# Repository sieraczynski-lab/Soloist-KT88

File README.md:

# Soloist 88 — stereofoniczny wzmacniacz lampowy na KT88

Projekt DIY wzmacniacza lampowego w stereo, opartego na układzie **Mullard 5-20** w wersji TubeMack „Soloist” przerobionej na **KT88**:

**EF86 → E88CC (odwracacz z długim ogonem, źródło prądowe DN2540) → 2× KT88 w układzie ultraliniowym, bias stały ≈ −80 V**

Do tego sterowanie na **ESP32-S3**: sekwencja włączania, pomiar prądu każdej KT88, automatyczna korekta biasu, przełącznik UL/trioda, przełącznik kolumn Marantz / Lampa i wejście trigger 12 V z amplitunera. Na wejściu **selektor 4 wejść z przekaźnikową drabinką głośności** 0–63 dB.

> ⚠️ **Wysokie napięcie.** W tym urządzeniu jest do ok. 560 V DC i 230 V AC. Kondensatory trzymają ładunek po wyłączeniu. Budujesz i uruchamiasz na własną odpowiedzialność, a pierwsze włączenia rób przez żarówkę szeregową, zgodnie z [procedurą uruchomienia](docs/06-uruchomienie.md).

## Najważniejsze parametry (z obliczeń, jeszcze nie z pomiarów)

| | |
|---|---|
| Moc | ok. 45 W na kanał na 4 Ω (zasilacz liczony na tę moc ciągłą) |
| Czułość | ok. 160 mV na pełną moc (dobierana R104) |
| Sprzężenie zwrotne | 14–16 dB |
| B+ | ok. 465 V, KT88 ok. 55 mA, ok. 25 W strat na lampę |
| Transformatory wyjściowe | Toroidy.pl TTG-KT88PP, 4 kΩ, UL |
| Transformator sieciowy | toroid 400 VA, jeden na oba kanały |

## Zawartość repozytorium

| Katalog | Co tam jest |
|---|---|
| [`docs/`](docs/) | dokumentacja: układ, zasilanie, sterowanie, płytki, obudowa, uruchomienie, zakupy, decyzje |
| [`hardware/pcb/`](hardware/pcb/) | gotowe pliki płytek: import do EasyEDA Pro, projekty KiCad, PDF-y rozmieszczenia, BOM do JLCPCB i LCSC, [`CZYTAJ_MNIE.txt`](hardware/pcb/CZYTAJ_MNIE.txt) |
| [`hardware/selektor/`](hardware/selektor/) | selektor wejść z drabinką głośności: projekt KiCad 8, eksport do EasyEDA Pro, BOM do JLCPCB i LCSC |
| [`hardware/case/`](hardware/case/) | obudowa: STEP (do Fusion 360), DXF do cięcia laserem, lista części, widoki |
| [`site/index.html`](site/index.html) | strona projektu: schematy, punkty pracy, sekwencja, zabezpieczenia, lista elementów |
| [`src/`](src/) | skrypty w Pythonie, które generują wszystko powyżej ([jak uruchomić](src/README.md)) |

## Płytki

| Płytka | Rozmiar | Ilość | Opis |
|---|---|---|---|
| `kanal` | 100 × 100 mm | 2 | EF86, E88CC, źródło prądowe, sieć biasu i sprzężenia zwrotnego |
| `zasilacz_siec` | 100 × 100 mm | 1 | miękki start K1/K2, bezpieczniki F2/F3, prostownik biasu, żarzenie |
| `zasilacz_hv` | 100 × 100 mm | 1 | K3/K4, mostek UF5408, kondensatory C1/C2, dzielnik pomiaru B+, LED HV |
| `sterowanie` | 100 × 100 mm | 1 | ESP32-S3, 2× ADS1115, MCP4728 + LM324, ULN2803, IRM-15-12; elementy SMD montuje JLCPCB |
| `ul` | 74 × 48 mm | 2 | przekaźniki UL/trioda (G2RL-2), jeden na KT88 |
| `glosniki` | 100 × 42 mm | 1 | przełącznik kolumn Marantz / Lampa (2× G2RL-2) |
| [`selektor`](hardware/selektor/) | 96 × 74 mm | 1 | 4 wejścia, drabinka 0–63 dB co 1 dB, mute fail-safe; 11× G6K-2F-Y, MCP23017 (I²C 0x20), 2× ULN2803; tylko 12 V |

## Dokumentacja

1. [Układ i punkty pracy](docs/01-uklad.md)
2. [Zasilanie i transformatory](docs/02-zasilanie.md)
3. [Sterowanie ESP32: korekta biasu, UL/trioda, kolumny, trigger](docs/03-sterowanie.md)
4. [Płytki PCB: EasyEDA, klasy sieci, JLCPCB](docs/04-plytki-pcb.md)
5. [Obudowa](docs/05-obudowa.md)
6. [Uruchomienie krok po kroku](docs/06-uruchomienie.md)
7. [Źródła sygnału i poziomy (WiiM, Marantz, selektor)](docs/07-zrodla-i-poziomy.md)
8. [Części i zakupy: lampy, przewody, przekaźniki, BOM](docs/08-czesci-i-zakupy.md)
9. [Historia decyzji i poprawek](docs/09-historia-decyzji.md)
10. [Do zrobienia / do sprawdzenia](docs/10-do-zrobienia.md)
11. [Selektor wejść i drabinka głośności](docs/11-selektor.md)
12. [Warianty lamp (opcjonalne)](docs/12-warianty-lamp.md)

## Stan

- Płytki: wersja **0.23**. Kanał po routingu w EasyEDA (wersja 0.21, od tamtej pory bez zmian). Pozostałe płytki do routingu.
- Selektor: wersja **0.5**, schemat gotowy, elementy rozmieszczone, do routingu ([szczegóły](docs/11-selektor.md)).
- Obudowa: wersja **0.4**.
- Strona projektu: wersja **0.12**.
- Program ESP32: opisany (sekwencje, algorytmy, progi), jeszcze nienapisany.
- Przed zamówieniem płytek: [lista rzeczy do sprawdzenia](docs/10-do-zrobienia.md#przed-zamówieniem-płytek).

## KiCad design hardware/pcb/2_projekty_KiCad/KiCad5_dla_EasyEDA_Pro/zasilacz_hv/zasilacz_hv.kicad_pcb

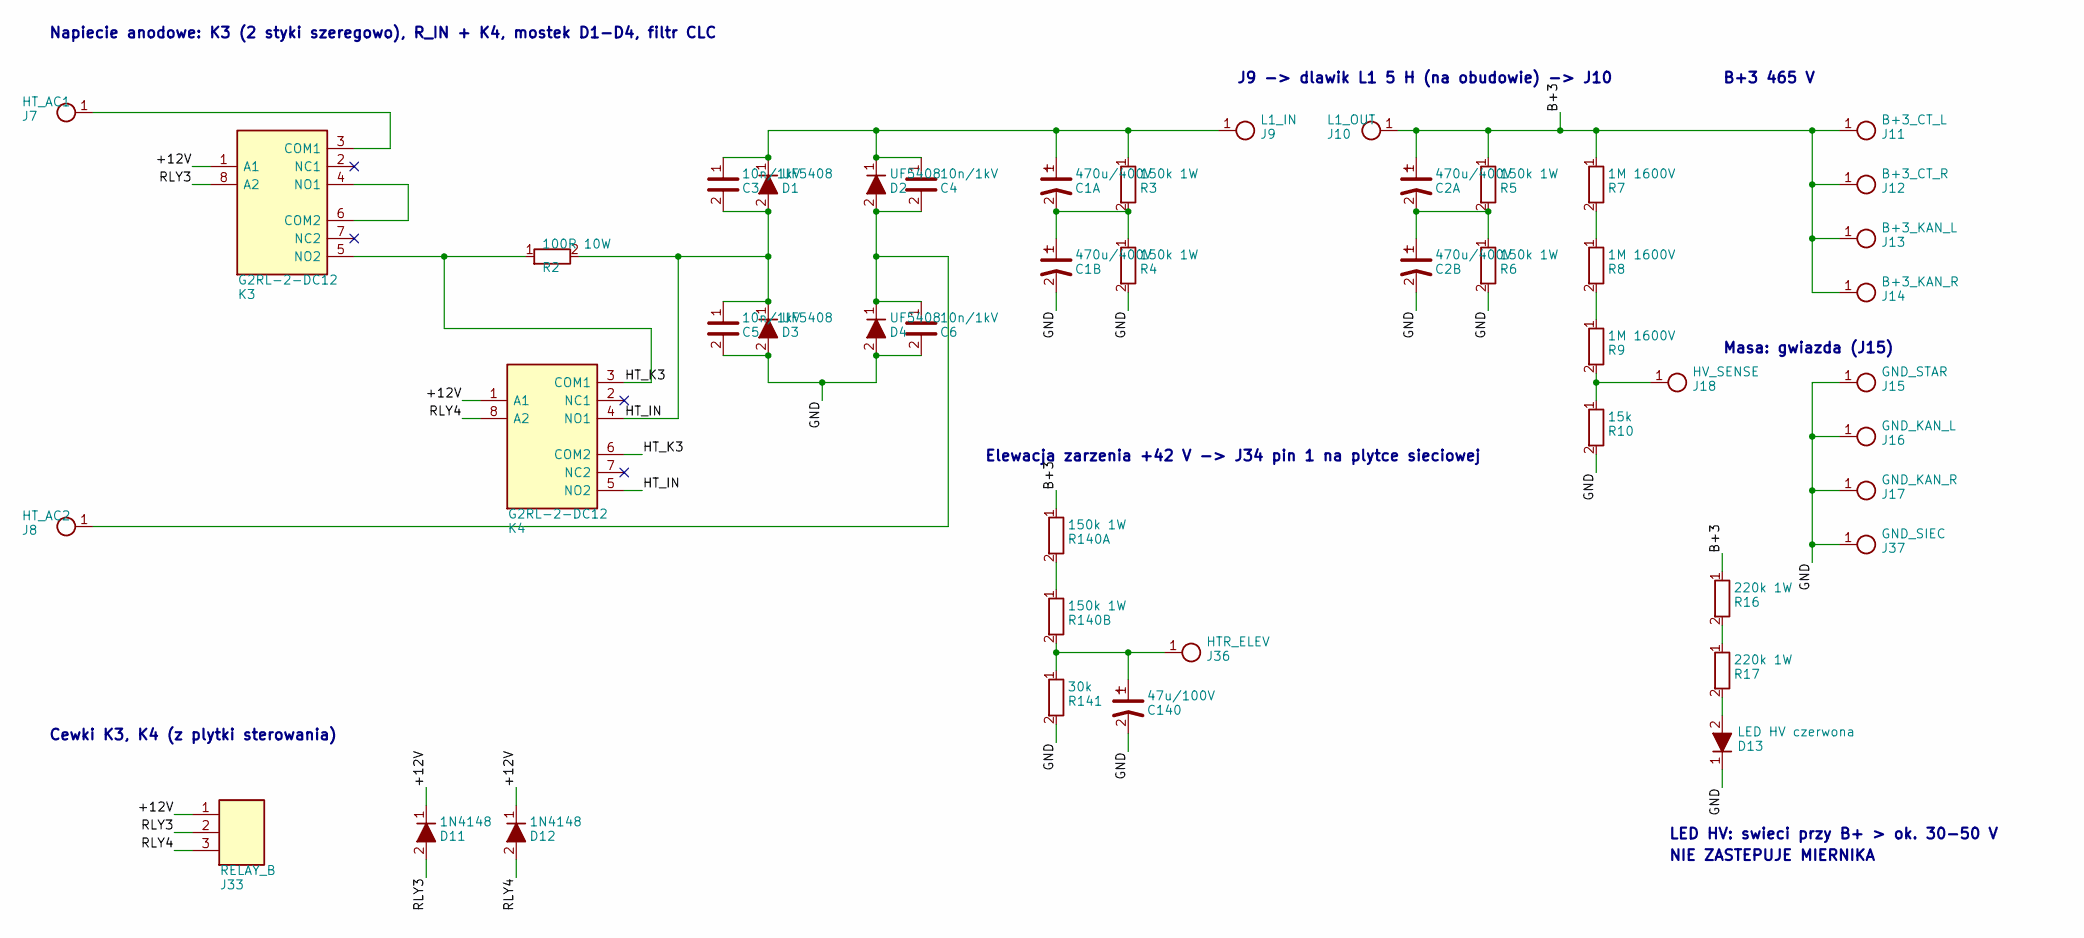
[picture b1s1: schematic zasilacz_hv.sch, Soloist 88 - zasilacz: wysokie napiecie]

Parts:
C1A, C1B, C2A, C2B: 470u/400V; CP_SnapIn_D30_P10
C3, C4, C5, C6: 10n/1kV; C_Disc_1kV_P10_V
C140: 47u/100V; CP_Radial_D10_P5
D1, D2, D3, D4: UF5408; D_DO-201_P15.24_V
D11: 1N4148; D_DO-35_P7.62
D12: 1N4148; D_DO-35_P7.62_V
D13: LED HV czerwona; LED_D3.0_P2.54
J7: HT_AC1; WirePad_4.5
J8: HT_AC2; WirePad_4.5
J9: L1_IN; WirePad_4.5
J10: L1_OUT; WirePad_4.5
J11: B+3_CT_L; WirePad_4.5
J12: B+3_CT_R; WirePad_4.5
J13: B+3_KAN_L; WirePad_4.5
J14: B+3_KAN_R; WirePad_4.5
J15: GND_STAR; WirePad_4.5
J16: GND_KAN_L; WirePad_4.5
J17: GND_KAN_R; WirePad_4.5
J18: HV_SENSE; WirePad_3.5
J33: RELAY_B; PinHeader_1x03_P2.54_H
J36: HTR_ELEV; WirePad_3.5
J37: GND_SIEC; WirePad_4.5
K3, K4: G2RL-2-DC12; Relay_DPDT_Omron_G2RL
R2: 100R 10W; R_Cement_10W_P55.88
R3, R4, R140A: 150k 1W; R_Axial_1W_P15.24_V
R5, R6, R140B: 150k 1W; R_Axial_1W_P15.24
R7, R8, R9: 1M 1600V; R_Axial_1W_P15.24_V
R10: 15k; R_Axial_0.5W_P12.7_V
R16, R17: 220k 1W; R_Axial_1W_P15.24
R141: 30k; R_Axial_0.5W_P12.7

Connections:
+12V: D11.1 (K), D12.1 (K), J33.1, K3.1 (A1), K4.1 (A1)
B+3: C2A.1, J10.1, J11.1, J12.1, J13.1, J14.1, R5.1, R7.1, R16.1, R140A.1
C1_MID: C1A.2, C1B.1, R3.2, R4.1
C2_MID: C2A.2, C2B.1, R5.2, R6.1
ELEV_MID: R140A.2, R140B.1
GND: C1B.2, C2B.2, C5.2, C6.2, C140.2, D3.2 (A), D4.2 (A), D13.1 (K), J15.1, J16.1, J17.1, J37.1, R4.2, R6.2, R10.2, R141.2
HTR_ELEV: C140.1, J36.1, R140B.2, R141.1
HT_AC1: J7.1, K3.3 (COM1)
HT_AC2: C4.2, C6.1, D2.2 (A), D4.1 (K), J8.1
HT_IN: C3.2, C5.1, D1.2 (A), D3.1 (K), K4.4 (NO1), K4.5 (NO2), R2.2
HT_K3: K3.5 (NO2), K4.3 (COM1), K4.6 (COM2), R2.1
HVS1: R7.2, R8.1
HVS2: R8.2, R9.1
HV_RAW: C1A.1, C3.1, C4.1, D1.1 (K), D2.1 (K), J9.1, R3.1
HV_SENSE: J18.1, R9.2, R10.1
K3_MID: K3.4 (NO1), K3.6 (COM2)
LED_A: D13.2 (A), R17.2
LED_M: R16.2, R17.1
RLY3: D11.2 (A), J33.2, K3.8 (A2)
RLY4: D12.2 (A), J33.3, K4.8 (A2)

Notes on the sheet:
Napiecie anodowe: K3 (2 styki szeregowo), R_IN + K4, mostek D1-D4, filtr CLC
J9 -> dlawik L1 5 H (na obudowie) -> J10
B+3 465 V
Elewacja zarzenia +42 V -> J34 pin 1 na plytce sieciowej
Cewki K3, K4 (z plytki sterowania)
LED HV: swieci przy B+ > ok. 30-50 V
NIE ZASTEPUJE MIERNIKA
Masa: gwiazda (J15)

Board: 2 copper layers, 51 parts (2 on the bottom side), 20 nets, no tracks yet.

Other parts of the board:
MH1, MH2, MH3, MH4: M3; MountingHole_M3

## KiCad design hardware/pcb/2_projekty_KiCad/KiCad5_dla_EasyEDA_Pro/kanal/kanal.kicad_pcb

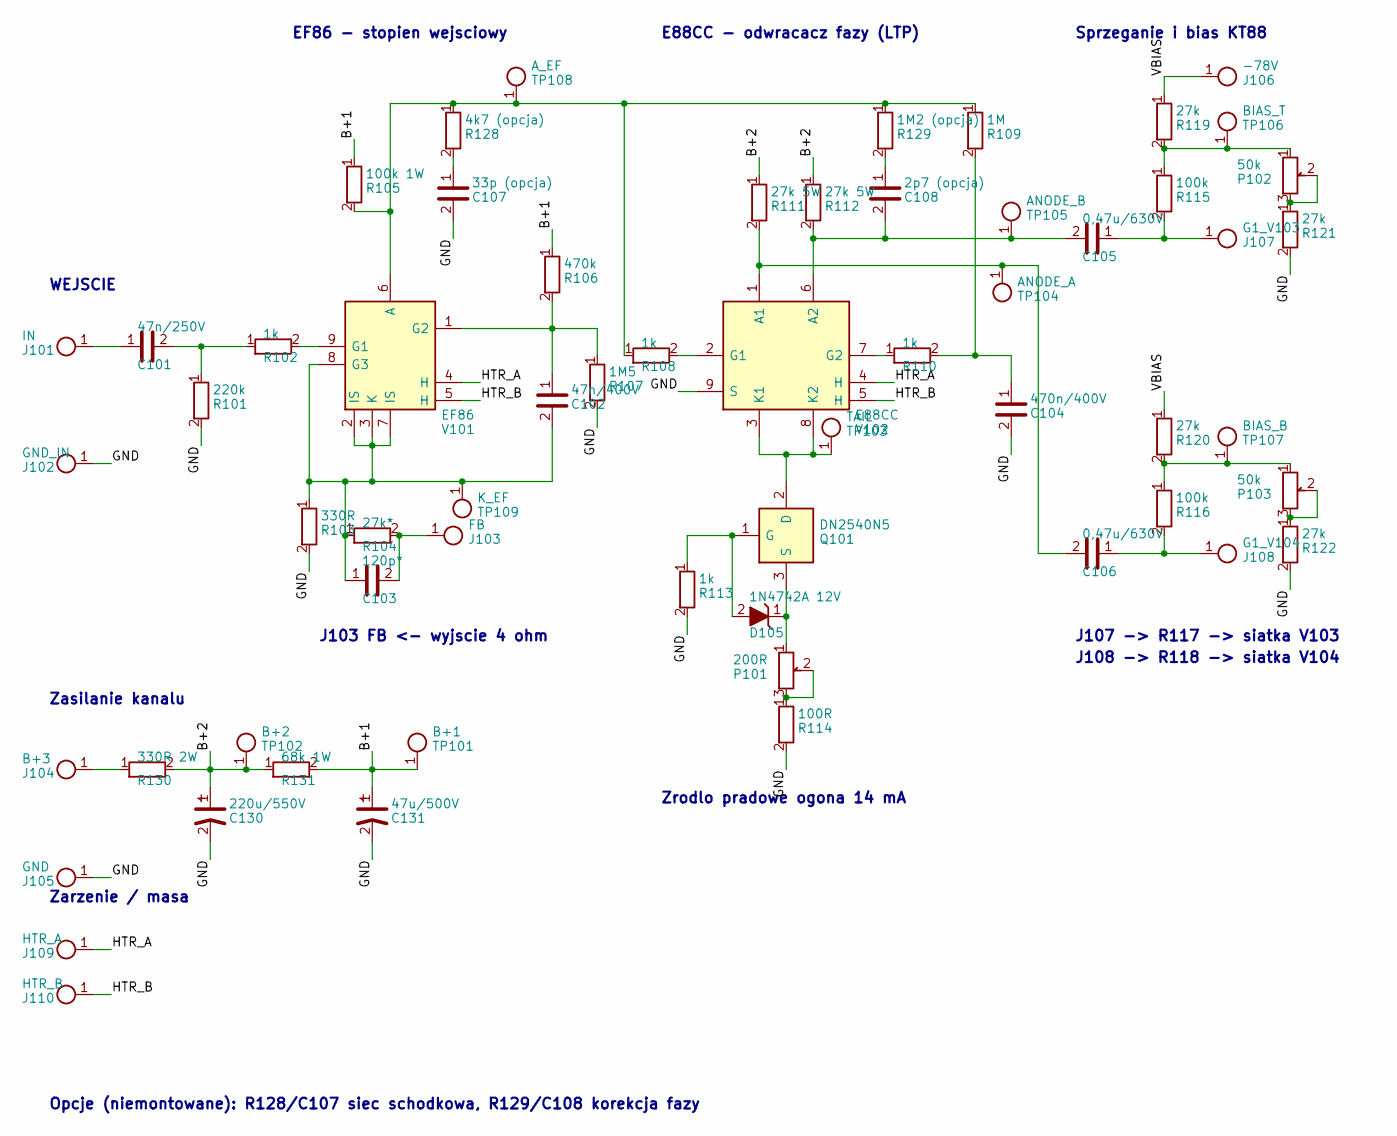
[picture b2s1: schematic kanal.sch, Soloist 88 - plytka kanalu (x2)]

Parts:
C101: 47n/250V; C_Box_P10_13x5
C102: 47n/400V; C_Box_P15_18x6_V
C103: 120p*; C_Box_P5_7x4
C104: 470n/400V; C_Box_P22.5_26.5x8.5_V
C105, C106: 0,47u/630V; C_Box_P27.5_31.5x11
C107: 33p (opcja); C_Box_P5_7x4
C108: 2p7 (opcja); C_Box_P5_7x4
C130: 220u/550V; CP_SnapIn_D35_P10
C131: 47u/500V; CP_Radial_D18_P7.5
D105: 1N4742A 12V; D_DO-41_P10.16
J101: IN; WirePad_3.5
J102: GND_IN; WirePad_3.5
J103: FB; WirePad_3.5
J104: B+3; WirePad_4.5
J105: GND; WirePad_4.5
J106: -78V; WirePad_3.5
J107: G1_V103; WirePad_3.5
J108: G1_V104; WirePad_3.5
J109: HTR_A; WirePad_3.5
J110: HTR_B; WirePad_3.5
P101: 200R; Trim_3296W
P102, P103: 50k; Trim_3296W
Q101: DN2540N5; TO-220_Vertical_SmallHeatsink
R101: 220k; R_Axial_0.5W_P12.7
R102, R108, R110, R113: 1k; R_Axial_0.5W_P12.7
R103: 330R; R_Axial_0.5W_P12.7
R104: 27k*; R_Axial_0.5W_P12.7_V
R105: 100k 1W; R_Axial_1W_P15.24_V
R106: 470k; R_Axial_0.5W_P12.7_V
R107: 1M5; R_Axial_0.5W_P12.7_V
R109: 1M; R_Axial_0.5W_P12.7_V
R111, R112: 27k 5W; R_Axial_5-7W_P35.56
R114: 100R; R_Axial_0.5W_P12.7
R115: 100k; R_Axial_0.5W_P12.7
R116: 100k; R_Axial_0.5W_P12.7_V
R119: 27k; R_Axial_0.5W_P12.7
R120, R121, R122: 27k; R_Axial_0.5W_P12.7_V
R128: 4k7 (opcja); R_Axial_0.5W_P12.7_V
R129: 1M2 (opcja); R_Axial_0.5W_P12.7
R130: 330R 2W; R_Axial_2W_P20.32_V
R131: 68k 1W; R_Axial_1W_P15.24
TP101: B+1; TestPoint_2
TP102: B+2; TestPoint_2
TP103: TAIL; TestPoint_2
TP104: ANODE_A; TestPoint_2
TP105: ANODE_B; TestPoint_2
TP106: BIAS_T; TestPoint_2
TP107: BIAS_B; TestPoint_2
TP108: A_EF; TestPoint_2
TP109: K_EF; TestPoint_2
V101: EF86; Noval_B9A_PCB
V102: E88CC; Noval_B9A_PCB

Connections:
ANODE_A: C106.2, R111.2, TP104.1, V102.1 (A1)
ANODE_B: C105.2, C108.2, R112.2, TP105.1, V102.6 (A2)
A_EF: R105.2, R108.1, R109.1, R128.1, R129.1, TP108.1, V101.6 (A)
B+1: C131.1, R105.1, R106.1, R131.2, TP101.1
B+2: C130.1, R111.1, R112.1, R130.2, R131.1, TP102.1
B+3: J104.1, R130.1
BIAS_B: P103.1, R116.1, R120.2, TP107.1
BIAS_T: P102.1, R115.1, R119.2, TP106.1
BMID_B: P103.2 (W), P103.3, R122.1
BMID_T: P102.2 (W), P102.3, R121.1
CC_MID: C108.1, R129.2
FB: C103.2, J103.1, R104.2
G1_EF: R102.2, V101.9 (G1)
G2_EF: C102.1, R106.2, R107.1, V101.1 (G2)
GND: C104.2, C107.2, C130.2, C131.2, J102.1, J105.1, R101.2, R103.2, R107.2, R113.2, R114.2, R121.2, R122.2, V102.9 (S)
GRID_B: C106.1, J108.1, R116.2
GRID_T: C105.1, J107.1, R115.2
G_A: R108.2, V102.2 (G1)
G_B: R110.1, V102.7 (G2)
HTR_A: J109.1, V101.4 (H), V102.4 (H)
HTR_B: J110.1, V101.5 (H), V102.5 (H)
IN: C101.1, J101.1
IN2: C101.2, R101.1, R102.1
K_EF: C102.2, C103.1, R103.1, R104.1, TP109.1, V101.2 (IS), V101.3 (K), V101.7 (IS), V101.8 (G3)
N_GB: C104.1, R109.2, R110.2
Q_G: D105.2 (A), Q101.1 (G), R113.1
Q_S: D105.1 (K), P101.1, Q101.3 (S)
RS_MID: P101.2 (W), P101.3, R114.1
STEP: C107.1, R128.2
TAIL: Q101.2 (D), TP103.1, V102.3 (K1), V102.8 (K2)
VBIAS: J106.1, R119.1, R120.1

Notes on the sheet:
WEJSCIE
EF86 - stopien wejsciowy
E88CC - odwracacz fazy (LTP)
Zrodlo pradowe ogona 14 mA
Sprzeganie i bias KT88
Zasilanie kanalu
Zarzenie / masa
J107 -> R117 -> siatka V103
J108 -> R118 -> siatka V104
J103 FB <- wyjscie 4 ohm
Opcje (niemontowane): R128/C107 siec schodkowa, R129/C108 korekcja fazy

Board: 2 copper layers, 65 parts (18 on the bottom side), 31 nets, no tracks yet.

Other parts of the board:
MH101, MH102, MH103, MH104, MH105: M3; MountingHole_M3

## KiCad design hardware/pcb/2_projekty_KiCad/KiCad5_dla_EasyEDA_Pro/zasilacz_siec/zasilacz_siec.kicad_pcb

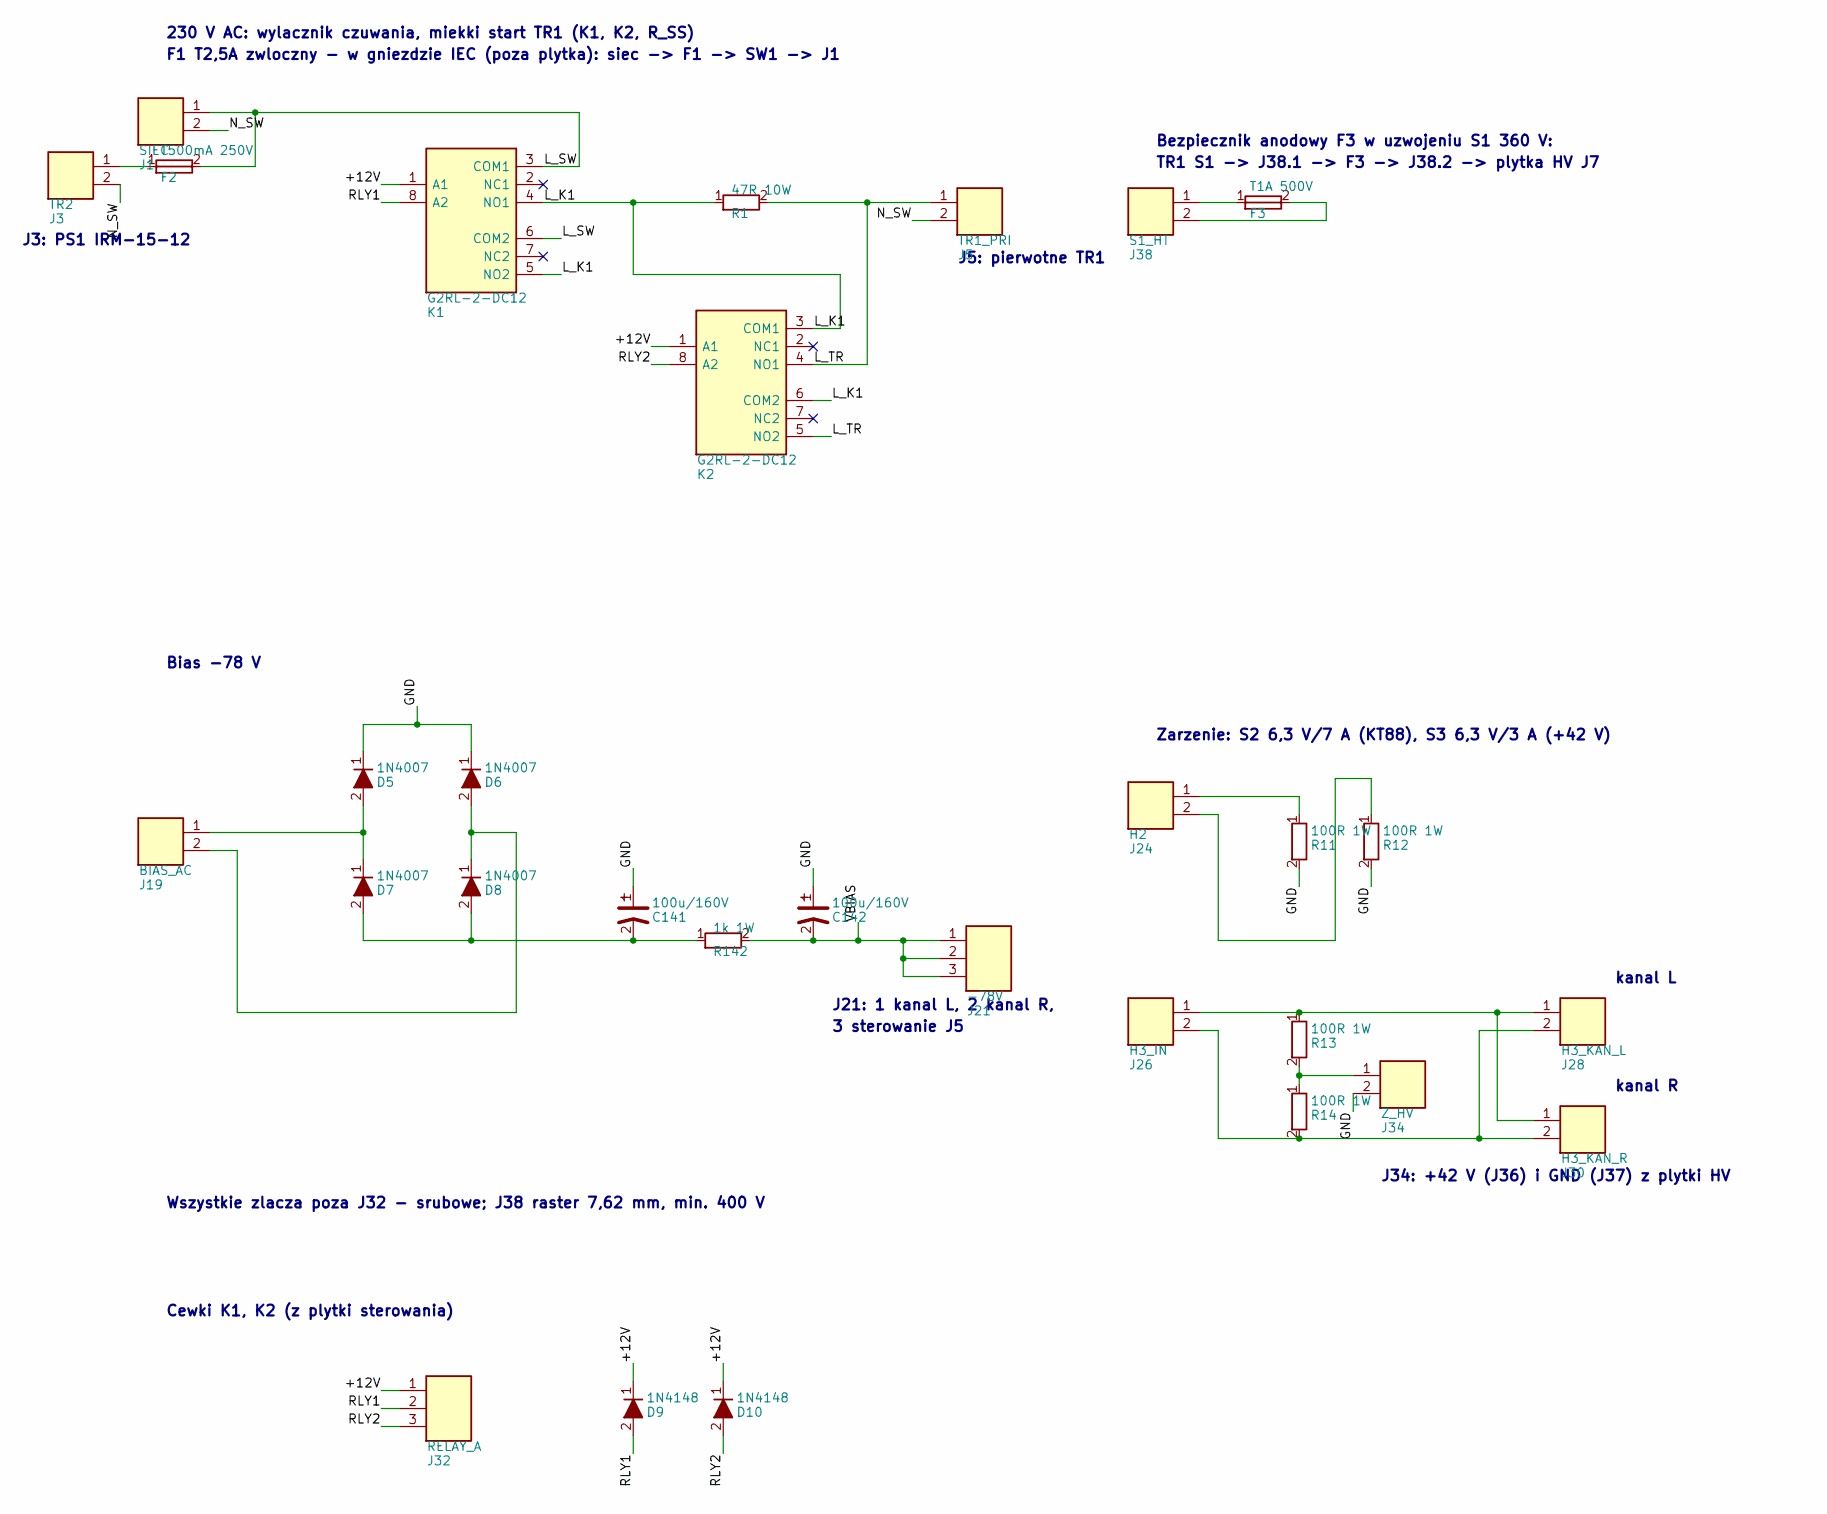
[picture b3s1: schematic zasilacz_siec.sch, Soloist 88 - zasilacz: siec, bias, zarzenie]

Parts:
C141, C142: 100u/160V; CP_Radial_D12.5_P5
D5, D6, D7, D8: 1N4007; D_DO-41_P10.16_V
D9, D10: 1N4148; D_DO-35_P7.62_V
F2: T500mA 250V; Fuseholder_5x20_Closed_P22.5
F3: T1A 500V; Fuseholder_5x20_P22.5_or_6.3x32_P30
J1: SIEC; TerminalBlock_1x02_P5.08_V
J3: TR2; TerminalBlock_1x02_P5.08_V
J5: TR1_PRI; TerminalBlock_1x02_P5.08_V
J19: BIAS_AC; TerminalBlock_1x02_P5.08_V
J21: -78V; TerminalBlock_1x03_P5.08_V
J24: H2; TerminalBlock_1x02_P5.08_V
J26: H3_IN; TerminalBlock_1x02_P5.08
J28: H3_KAN_L; TerminalBlock_1x02_P5.08
J30: H3_KAN_R; TerminalBlock_1x02_P5.08
J32: RELAY_A; PinHeader_1x03_P2.54
J34: Z_HV; TerminalBlock_1x02_P5.08
J38: S1_HT; TerminalBlock_1x02_P7.62_V
K1, K2: G2RL-2-DC12; Relay_DPDT_Omron_G2RL
R1: 47R 10W; R_Cement_10W_P55.88
R11, R12, R13, R14: 100R 1W; R_Axial_1W_P15.24_V
R142: 1k 1W; R_Axial_1W_P15.24_V

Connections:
+12V: D9.1 (K), D10.1 (K), J32.1, K1.1 (A1), K2.1 (A1)
B_AC1: D5.2 (A), D7.1 (K), J19.1
B_AC2: D6.2 (A), D8.1 (K), J19.2
GND: C141.1, C142.1, D5.1 (K), D6.1 (K), J34.2, R11.2, R12.2
H2_A: J24.1, R11.1
H2_B: J24.2, R12.1
H3_A: J26.1, J28.1, J30.1, R13.1
H3_B: J26.2, J28.2, J30.2, R14.2
HTR_ELEV: J34.1, R13.2, R14.1
HT_F: F3.2, J38.2
HT_TR: F3.1, J38.1
L_K1: K1.4 (NO1), K1.5 (NO2), K2.3 (COM1), K2.6 (COM2), R1.1
L_SW: F2.2, J1.1, K1.3 (COM1), K1.6 (COM2)
L_TR: J5.1, K2.4 (NO1), K2.5 (NO2), R1.2
L_TR2: F2.1, J3.1
N_SW: J1.2, J3.2, J5.2
RLY1: D9.2 (A), J32.2, K1.8 (A2)
RLY2: D10.2 (A), J32.3, K2.8 (A2)
VBIAS: C142.2, J21.1, J21.2, J21.3, R142.2
VB_RAW: C141.2, D7.2 (A), D8.2 (A), R142.1

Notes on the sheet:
230 V AC: wylacznik czuwania, miekki start TR1 (K1, K2, R_SS)
F1 T2,5A zwloczny - w gniezdzie IEC (poza plytka): siec -> F1 -> SW1 -> J1
J5: pierwotne TR1
J3: PS1 IRM-15-12
Bezpiecznik anodowy F3 w uzwojeniu S1 360 V:
TR1 S1 -> J38.1 -> F3 -> J38.2 -> plytka HV J7
Bias -78 V
J21: 1 kanal L, 2 kanal R,
3 sterowanie J5
Zarzenie: S2 6,3 V/7 A (KT88), S3 6,3 V/3 A (+42 V)
kanal L
kanal R
J34: +42 V (J36) i GND (J37) z plytki HV
Cewki K1, K2 (z plytki sterowania)
Wszystkie zlacza poza J32 - srubowe; J38 raster 7,62 mm, min. 400 V

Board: 2 copper layers, 34 parts (0 on the bottom side), 20 nets, no tracks yet.

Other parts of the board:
MH1, MH2, MH3, MH4: M3; MountingHole_M3

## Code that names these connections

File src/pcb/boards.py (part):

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    A("J110", "HTR_B", "PAD", ["HTR_B"], g_con, "zarzenie 6,3 V")
    A("C101", "47n/250V", "C", ["IN", "IN2"], g_in)
    A("R101", "220k", "R", ["IN2", "GND"], g_in)
    A("R102", "1k", "R", ["IN2", "G1_EF"], g_in, "przy podstawce, pin 9")
    A("V101", "EF86", "EF86",
      {"9": "G1_EF", "8": "K_EF", "3": "K_EF", "2": "K_EF", "7": "K_EF", "6": "A_EF", "1": "G2_EF", "4": "HTR_A", "5": "HTR_B"}, g_ef,
      "montaz antymikrofonowy; pin 2,7 ekran do katody")
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    A("V102", "E88CC", "E88CC",
      {"2": "G_A", "1": "ANODE_A", "3": "TAIL", "9": "GND", "7": "G_B", "6": "ANODE_B", "8": "TAIL", "4": "HTR_A", "5": "HTR_B"}, g_ltp,
      "E88CC/6922/6N23P-EV; wariant B: 6N6P")
    A("R108", "1k", "R", ["A_EF", "G_A"], g_ltp, "przy podstawce, pin 2")
    A("R109", "1M", "R", ["A_EF", "N_GB"], g_ltp)
    A("R110", "1k", "R", ["G_B", "N_GB"], g_ltp, "przy podstawce, pin 7")
    A("C104", "470n/400V", "C", ["N_GB", "GND"], g_ltp)
    A("R111", "27k 5W", "R", ["B+2", "ANODE_A"], g_ltp, "para 1%; pola pod 7W (wariant B 12k)")
    A("R112", "27k 5W", "R", ["B+2", "ANODE_B"], g_ltp, "para 1%; pola pod 7W (wariant B 12k)")
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        ("R14", "100R 1W", "R", ["HTR_ELEV", "H3_B"], g_h, ""),
        ("J28", "H3_KAN_L", "CONN_2", ["H3_A", "H3_B"], g_h, "zlacze srubowe: zarzenie kanalu L"),
        ("J30", "H3_KAN_R", "CONN_2", ["H3_A", "H3_B"], g_h, "zlacze srubowe: zarzenie kanalu R"),
        ("J32", "RELAY_A", "CONN_3", ["+12V", "RLY1", "RLY2"], g_r, "z plytki sterowania (J2 piny 1,2,3)"),
        ("D9", "1N4148", "D", {"1": "+12V", "2": "RLY1"}, g_r, ""),
        ("D10", "1N4148", "D", {"1": "+12V", "2": "RLY2"}, g_r, ""),
        ("J34", "Z_HV", "CONN_2", ["HTR_ELEV", "GND"], g_c, "zlacze srubowe: 1 +42 V z plytki HV J36, 2 GND z plytki HV J37 (gwiazda)"),
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                                         "CEWKI K3/K4", "ZLACZA", "OTWORY")
    g_bl = "LED HV"
    comps = [
        ("J7", "HT_AC1", "PAD", ["HT_AC1"], g_ht, "S1 360 V przez F3 (plytka sieciowa J38 pin 2)"),
        ("J8", "HT_AC2", "PAD", ["HT_AC2"], g_ht, "S1 360 V"),
        ("K3", "G2RL-2-DC12", "RELAY_G2RL", {"1": "+12V", "8": "RLY3", "3": "HT_AC1", "2": None, "4": "K3_MID",
                                       "6": "K3_MID", "7": None, "5": "HT_K3"}, g_ht, "Omron G2RL-2, dwa styki szeregowo (360 V AC)"),
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        ("R140B", "150k 1W", "R", ["ELEV_MID", "HTR_ELEV"], g_e, "elewacja, druga polowa"),
        ("R141", "30k", "R", ["HTR_ELEV", "GND"], g_e, ""),
        ("C140", "47u/100V", "CP", ["HTR_ELEV", "GND"], g_e, ""),
        ("J36", "HTR_ELEV", "PAD", ["HTR_ELEV"], g_e, "do plytki sieciowej (J34 pin 1)"),
        ("J33", "RELAY_B", "CONN_3", ["+12V", "RLY3", "RLY4"], g_r, "z plytki sterowania (J2 piny 1,4,5)"),
        ("D11", "1N4148", "D", {"1": "+12V", "2": "RLY3"}, g_r, ""),
        ("D12", "1N4148", "D", {"1": "+12V", "2": "RLY4"}, g_r, ""),
        ("R16", "220k 1W", "R", ["B+3", "LED_M"], g_bl, "LED HV, ok. 1 mA"),
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         {"1": "DRV1", "2": "DRV2", "3": "DRV3", "4": "DRV4", "5": "DRV5", "6": "DRV6", "7": "DRV7", "8": "GND",
          "18": "RLY1", "17": "RLY2", "16": "RLY3", "15": "RLY4", "14": "MUTE", "13": "RLY_UL", "12": "RLY_SPK", "11": None,
          "9": "GND", "10": "+12V"}, g_drv, "UTC ULN2803G-S18-R, SOP-18 (7,5 mm) - LCSC C33924"),
        ("J2", "RELAY", "CONN_5", ["+12V", "RLY1", "RLY2", "RLY3", "RLY4"], g_drv, "do plytek zasilacza (piny 1,2,3 -> siec; 1,4,5 -> HV)"),
        ("J3", "MUTE", "CONN_2", ["+12V", "MUTE"], g_drv, "przekaznik MUTE w przedwzmacniaczu"),
        ("J11", "UL_TRIODA", "CONN_4", ["+12V", "RLY_UL", "+12V", "RLY_UL"], g_drv, "1-2 plytka UL kanalu L, 3-4 kanalu P (J3 na plytce UL)"),
        ("J13", "GLOSNIKI", "CONN_2", ["+12V", "RLY_SPK"], g_drv, "cewki przelacznika glosnikow (plytka glosniki J7)"),
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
